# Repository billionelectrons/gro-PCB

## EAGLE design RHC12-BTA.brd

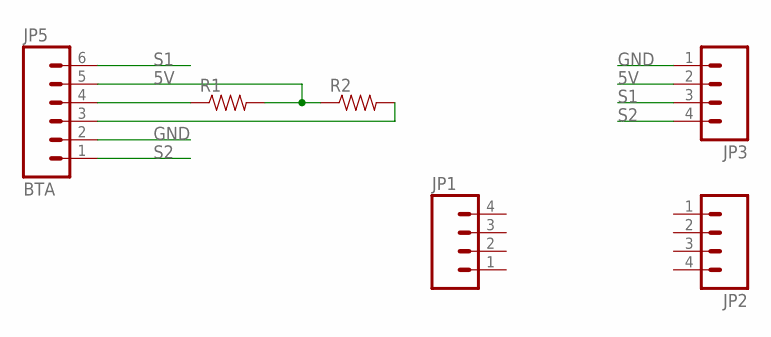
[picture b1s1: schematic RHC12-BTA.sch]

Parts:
JP1, JP2, JP3: M04SMD; 1X04-SMD
JP5: BTA
R1, R2: RESISTOR0603-RES; 0603-RES

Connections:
5V: JP3.2, JP5.5, R1.2, R2.1
GND: JP3.1, JP5.2
unnamed: JP5.4, R1.1
unnamed: JP5.3, R2.2
S1: JP3.3, JP5.6
S2: JP3.4, JP5.1

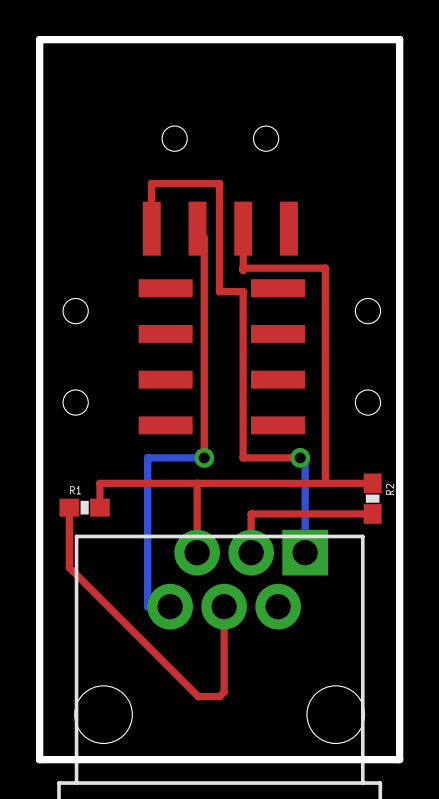
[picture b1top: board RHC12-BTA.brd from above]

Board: 2 copper layers, 20.0 x 40.0 mm, 6 parts (0 on the bottom side), 6 nets.

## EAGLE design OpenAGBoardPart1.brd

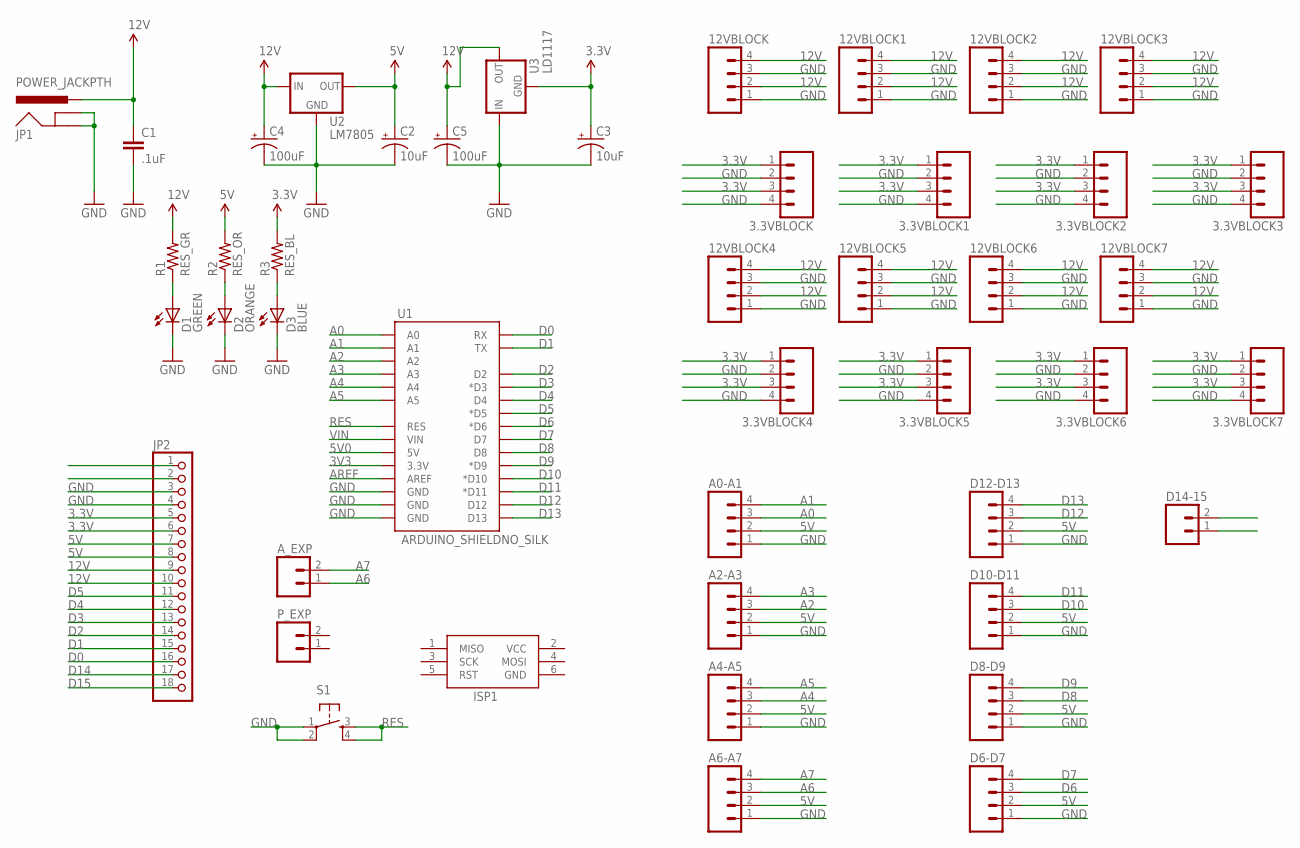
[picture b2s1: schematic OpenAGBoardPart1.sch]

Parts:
3.3VBLOCK, 3.3VBLOCK1, 3.3VBLOCK2, 3.3VBLOCK3, 3.3VBLOCK4, 3.3VBLOCK5, 3.3VBLOCK6, 3.3VBLOCK7, 12VBLOCK, 12VBLOCK1, 12VBLOCK2, 12VBLOCK3, 12VBLOCK4, 12VBLOCK5, 12VBLOCK6, 12VBLOCK7: M04NO_SILK_ALL_ROUND; 1X04_NO_SILK_ALL_ROUND
A0-A1, A2-A3, A4-A5, A6-A7: M04NO_SILK_ALL_ROUND; 1X04_NO_SILK_ALL_ROUND
A_EXP: M02PTH; 1X02
C1: .1uF; CAP-PTH-SMALL
C2, C3: 10uF; CPOL-RADIAL-10UF-25V
C4, C5: 100uF; CPOL-RADIAL-100UF-25V
D1: GREEN; LED5MM
D2: ORANGE; LED5MM
D3: BLUE; LED5MM
D6-D7, D8-D9, D10-D11, D12-D13: M04NO_SILK_ALL_ROUND; 1X04_NO_SILK_ALL_ROUND
D14-15: M02PTH; 1X02
ISP1: AVRISP-6; AVRISP
JP1: POWER_JACKPTH; POWER_JACK_PTH
JP2: PINHD-1X18-BIG; 1X18-BIG
P_EXP: M02PTH; 1X02
R1: RES_GR; AXIAL-0.4
R2: RES_OR; AXIAL-0.4
R3: RES_BL; AXIAL-0.4
S1: TAC_SWITCHPTH; TACTILE-PTH
U1: ARDUINO_SHIELDNO_SILK; DUEMILANOVE_VIAS
U2: LM7805; TO220-IGO
U3: LD1117; TO220-IGO

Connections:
3.3V: 3.3VBLOCK.1, 3.3VBLOCK.3, 3.3VBLOCK1.1, 3.3VBLOCK1.3, 3.3VBLOCK2.1, 3.3VBLOCK2.3, 3.3VBLOCK3.1, 3.3VBLOCK3.3, 3.3VBLOCK4.1, 3.3VBLOCK4.3, 3.3VBLOCK5.1, 3.3VBLOCK5.3, 3.3VBLOCK6.1, 3.3VBLOCK6.3, 3.3VBLOCK7.1, 3.3VBLOCK7.3, C3.1 (+), JP2.5, JP2.6, R3.P$2 (2), U3.GND
3V3: U1.3.3V
5V: A0-A1.2, A2-A3.2, A4-A5.2, A6-A7.2, C2.1 (+), D6-D7.2, D8-D9.2, D10-D11.2, D12-D13.2, JP2.7, JP2.8, R2.P$2 (2), U2.OUT
5V0: U1.5V
12V: 12VBLOCK.2, 12VBLOCK.4, 12VBLOCK1.2, 12VBLOCK1.4, 12VBLOCK2.2, 12VBLOCK2.4, 12VBLOCK3.2, 12VBLOCK3.4, 12VBLOCK4.2, 12VBLOCK4.4, 12VBLOCK5.2, 12VBLOCK5.4, 12VBLOCK6.2, 12VBLOCK6.4, 12VBLOCK7.2, 12VBLOCK7.4, C1.1, C4.1 (+), C5.1 (+), JP1.PWR, JP2.9, JP2.10, R1.P$2 (2), U2.IN, U3.OUT
A0: A0-A1.3, U1.A0
A1: A0-A1.4, U1.A1
A2: A2-A3.3, U1.A2
A3: A2-A3.4, U1.A3
A4: A4-A5.3, U1.A4
A5: A4-A5.4, U1.A5
A6: A6-A7.3, A_EXP.1
A7: A6-A7.4, A_EXP.2
AREF: U1.AREF
CONTINUITY_STRIP: JP2.1
D0: JP2.16, U1.RX
D1: JP2.15, U1.TX
D2: JP2.14, U1.D2
D3: JP2.13, U1.D3 (*D3)
D4: JP2.12, U1.D4
D5: JP2.11, U1.D5 (*D5)
D6: D6-D7.3, U1.D6 (*D6)
D7: D6-D7.4, U1.D7
D8: D8-D9.3, U1.D8
D9: D8-D9.4, U1.D9 (*D9)
D10: D10-D11.3, U1.D10 (*D10)
D11: D10-D11.4, U1.D11 (*D11)
D12: D12-D13.3, U1.D12
D13: D12-D13.4, U1.D13
D14: D14-15.1, JP2.17
D15: D14-15.2, JP2.18
GND: 3.3VBLOCK.2, 3.3VBLOCK.4, 3.3VBLOCK1.2, 3.3VBLOCK1.4, 3.3VBLOCK2.2, 3.3VBLOCK2.4, 3.3VBLOCK3.2, 3.3VBLOCK3.4, 3.3VBLOCK4.2, 3.3VBLOCK4.4, 3.3VBLOCK5.2, 3.3VBLOCK5.4, 3.3VBLOCK6.2, 3.3VBLOCK6.4, 3.3VBLOCK7.2, 3.3VBLOCK7.4, 12VBLOCK.1, 12VBLOCK.3, 12VBLOCK1.1, 12VBLOCK1.3, 12VBLOCK2.1, 12VBLOCK2.3, 12VBLOCK3.1, 12VBLOCK3.3, 12VBLOCK4.1, 12VBLOCK4.3, 12VBLOCK5.1, 12VBLOCK5.3, 12VBLOCK6.1, 12VBLOCK6.3, 12VBLOCK7.1, 12VBLOCK7.3, A0-A1.1, A2-A3.1, A4-A5.1, A6-A7.1, C1.2, C2.2 (-), C3.2 (-), C4.2 (-), C5.2 (-), D1.K (C), D2.K (C), D3.K (C), D6-D7.1, D8-D9.1, D10-D11.1, D12-D13.1, ISP1.6 (GND), JP1.GND, JP1.GNDBREAK, JP2.3, JP2.4, S1.1, S1.2, U1.GND@0 (GND), U1.GND@1 (GND), U1.GND@2 (GND), U2.GND, U3.IN
unnamed: D1.A, R1.P$1 (1)
unnamed: D2.A, R2.P$1 (1)
unnamed: D3.A, R3.P$1 (1)
RES: S1.3, S1.4, U1.RES
VCC: ISP1.2 (VCC)
VIN: U1.VIN

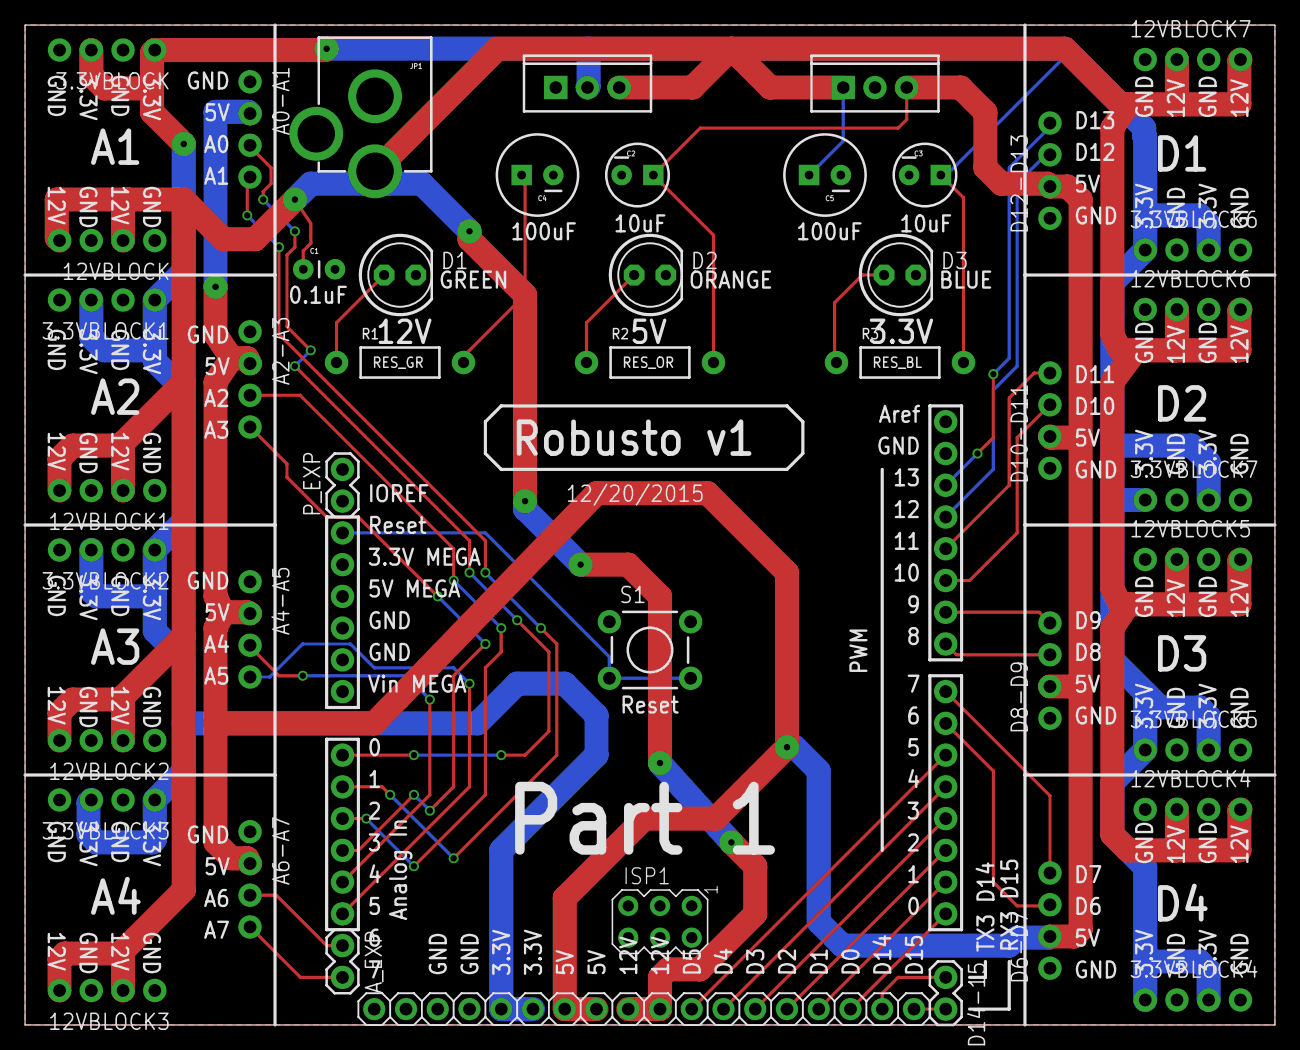
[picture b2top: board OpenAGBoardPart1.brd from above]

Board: 2 copper layers, 100.0 x 80.0 mm, 45 parts (0 on the bottom side), 32 nets.

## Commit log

2016-01-21 Added schematic and board files
2016-01-21 Corrected LED color
2016-01-21 added photos of build and partial BOM
2016-01-25 Create LICENSE
2016-01-31 Switched RHC12 to SMD except for the BTA part
2016-01-31 Uh...

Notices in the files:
parts and their libraries:
SparkFun-Connectors: Licensing: Creative Commons ShareAlike 4.0 International - https://creativecommons.org/licenses/by-sa/4.0
SparkFun-Connectors: Licensing: CC v3.0 Share-Alike You are welcome to use this library for commercial purposes.
